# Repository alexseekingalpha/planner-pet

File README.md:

Planner Pet: By Alexander Smallwood
Welcome to my project - Planner pet! 
Inspired by my struggles with ADHD I wanted to mkae a deivce to motivate others and I to complete tasks regardless of what the task is. 
Take homework for example. Homework is so hard to complete as there is no instant reward, you must wait to finish the problem to recieve the dopamine of completing such homework. 
To fix this I hypothesise that a digital pet will create a bond to the user motivating them to complete tasks to keep the pet alive! Like a tamagotchi!

The process is simple and fun:
Complete tasks and your pet earns XP which lets it grow through life stages, and unlocks cosmetics. Miss tasks and it regresses eventually going dormant.
To enhance attachment, each pet is generated from a random seed so everyone has a unique pet!

Hardware:
MCU: Esp32-S3-Wroom-1-N8
Display: st7789 240x250 tft spi 
RTC: DS3231 
Power: 500mah lipo whith BQ24040 charging via USBC, TLV75801 ldo to regualate the power to the MCU
Input: 4 button dpad with + 2 standalone buttons for 'select' and 'back'
All KiCad files will be uploaded (Using KiCad 9)

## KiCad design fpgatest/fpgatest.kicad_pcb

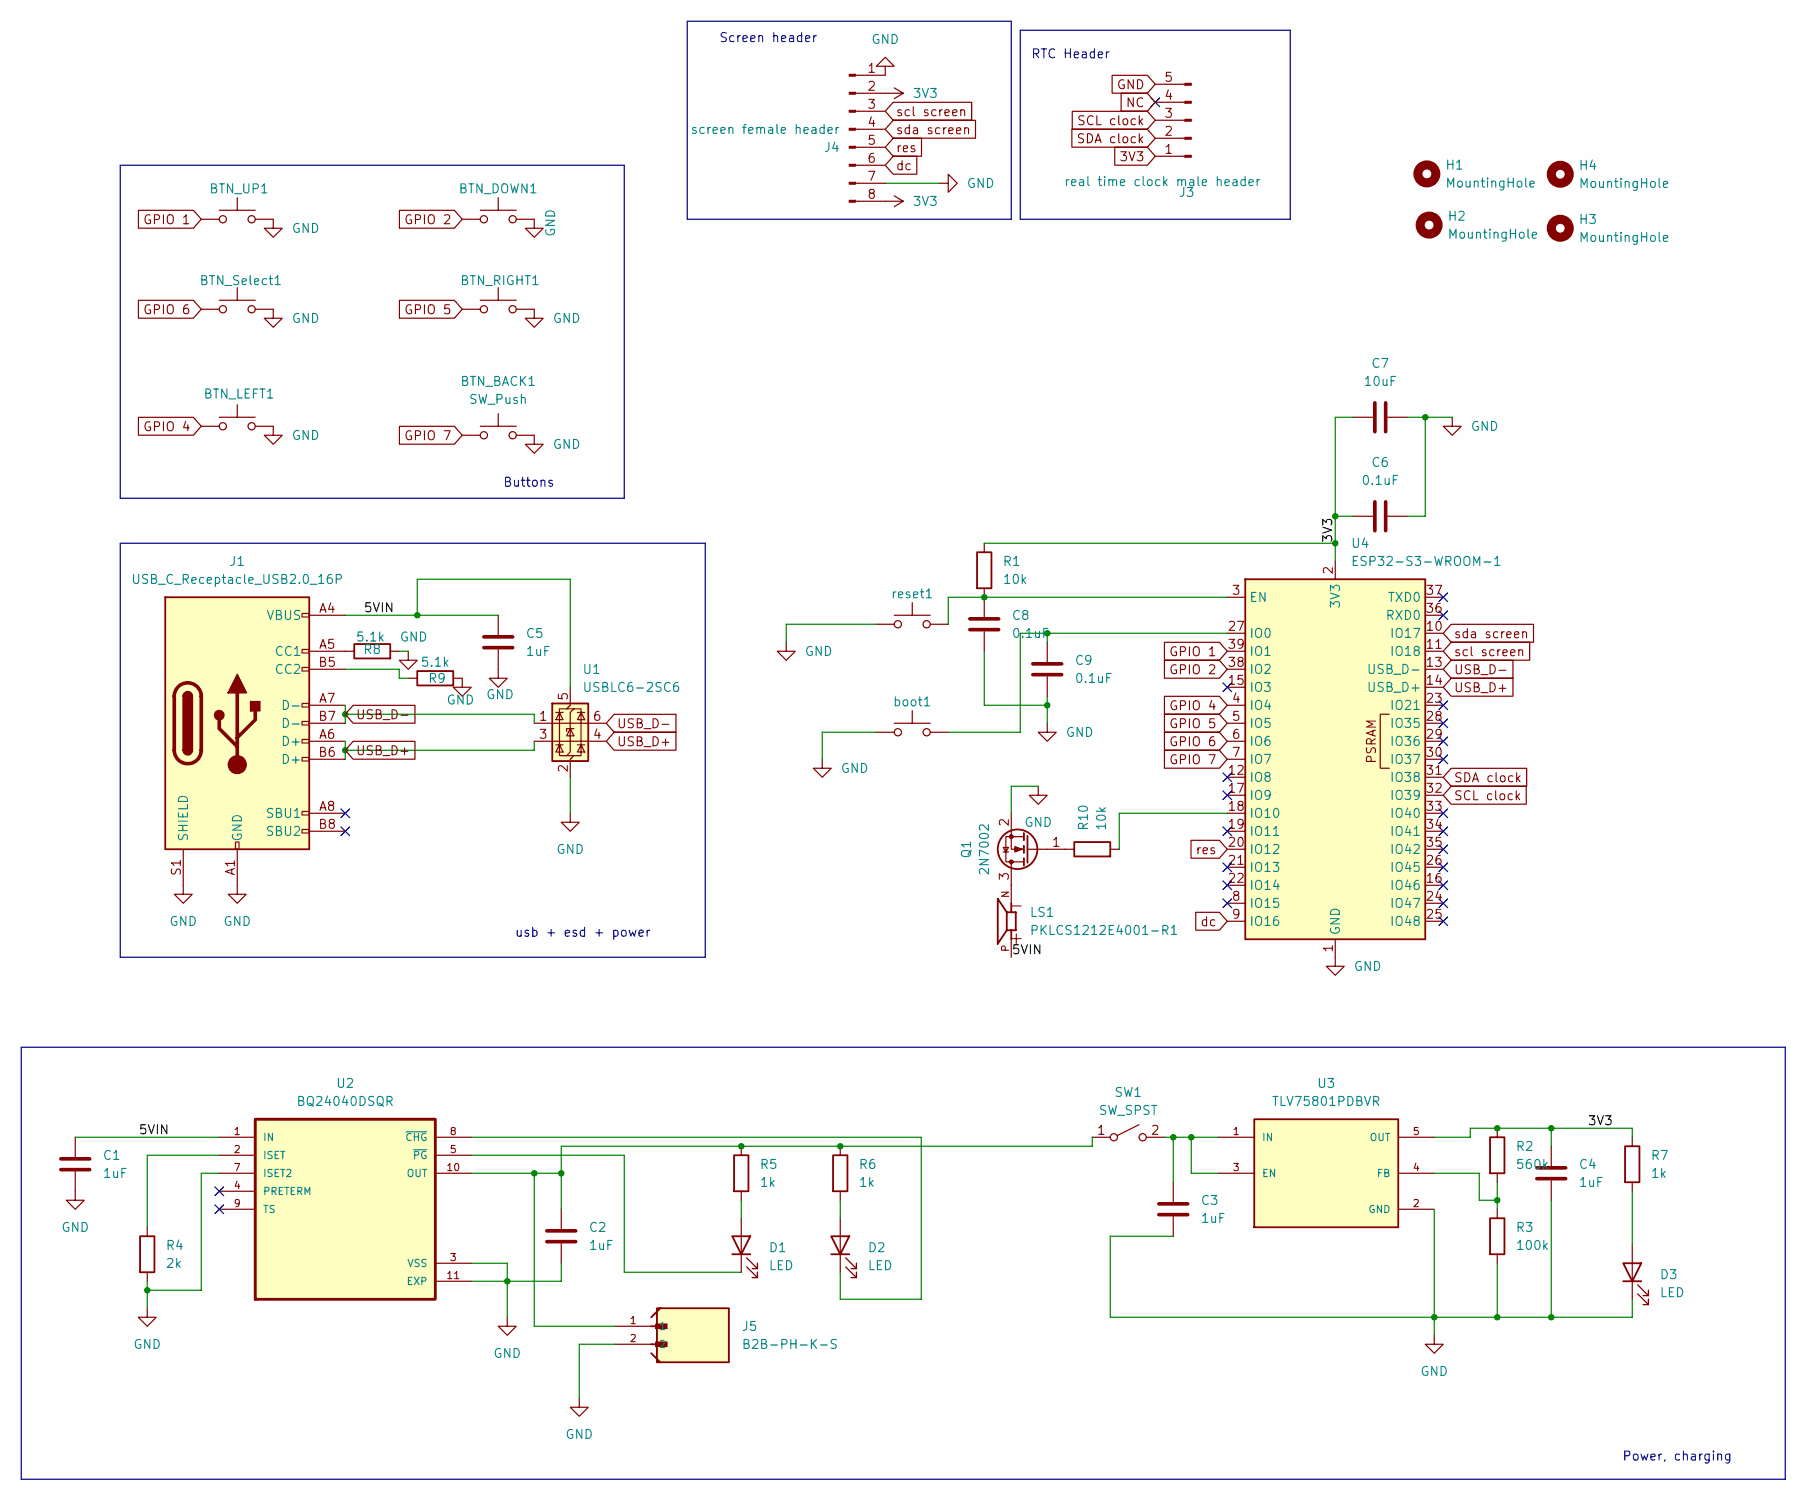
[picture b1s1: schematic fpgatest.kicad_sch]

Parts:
BTN_BACK1: SW_Push; SW_Push_1P1T_NO_CK_KMR2
BTN_DOWN1: SW_Push; SW_Push_1P1T_NO_CK_KMR2
BTN_LEFT1: SW_Push; SW_Push_1P1T_NO_CK_KMR2
BTN_RIGHT1: SW_Push; SW_Push_1P1T_NO_CK_KMR2
BTN_Select1: SW_Push; SW_Push_1P1T_NO_CK_KMR2
BTN_UP1: SW_Push; SW_Push_1P1T_NO_CK_KMR2
C1, C2, C3, C4, C5: 1uF; C_0603_1608Metric
C6, C8, C9: 0.1uF; C_0603_1608Metric
C7: 10uF; C_0603_1608Metric
D1, D2, D3: LED; LED_0603_1608Metric
H1, H2, H3, H4: MountingHole; MountingHole_2.2mm_M2
J1: USB_C_Receptacle_USB2.0_16P; USB_C_Receptacle_GCT_USB4105-xx-A_16P_TopMnt_Horizontal
J3: real time clock male header; PinHeader_1x05_P2.54mm_Vertical
J4: screen female header; PinSocket_1x08_P2.54mm_Vertical
J5: B2B-PH-K-S; JST_B2B-PH-K-S
LS1: PKLCS1212E4001-R1; SPKR_PKLCS1212E4001-R1; PARTREV January 22, 2018
Q1: 2N7002; SOT-23
R1, R10: 10k; R_0603_1608Metric
R2: 560k; R_0603_1608Metric
R3: 100k; R_0603_1608Metric
R4: 2k; R_0603_1608Metric
R5, R6, R7: 1k; R_0603_1608Metric
R8, R9: 5.1k; R_0603_1608Metric
SW1: SW_SPST; SW_SPDT_PCM12
U1: USBLC6-2SC6; SOT-23-6
U2: BQ24040DSQR; SON40P200X200X80-11N
U3: TLV75801PDBVR; SOT95P280X145-5N; PARTREV D
U4: ESP32-S3-WROOM-1
boot1: SW_Push; SW_Push_1P1T_NO_CK_KMR2
reset1: SW_Push; SW_Push_1P1T_NO_CK_KMR2

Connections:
3V3: C4.1, C6.1, C7.1, J3.1, J4.2, J4.8, R1.1, R2.1, R7.1, U3.5 (OUT), U4.2 (3V3)
/5VIN: C1.1, C5.1, J1.A4 (VBUS), J1.A9 (VBUS), J1.B4 (VBUS), J1.B9 (VBUS), LS1.P, U1.5 (VBUS), U2.1 (IN)
GND: BTN_BACK1.2, BTN_DOWN1.2, BTN_LEFT1.2, BTN_RIGHT1.2, BTN_Select1.2, BTN_UP1.2, C1.2, C2.2, C3.2, C4.2, C5.2, C6.2, C7.2, C8.2, C9.2, D3.1 (K), J1.A1 (GND), J1.A12 (GND), J1.B1 (GND), J1.B12 (GND), J1.S1 (SHIELD), J3.5, J4.1, J4.7, J5.2, Q1.2 (S), R3.2, R4.2, R8.2, R9.2, U1.2 (GND), U2.3 (VSS), U2.7 (ISET2), U2.11 (EXP), U3.2 (GND), U4.1 (GND), U4.40 (GND), U4.41 (GND), boot1.1, reset1.1
GPIO 1: BTN_UP1.1, U4.39 (IO1)
GPIO 2: BTN_DOWN1.1, U4.38 (IO2)
GPIO 4: BTN_LEFT1.1, U4.4 (IO4)
GPIO 5: BTN_RIGHT1.1, U4.5 (IO5)
GPIO 6: BTN_Select1.1, U4.6 (IO6)
GPIO 7: BTN_BACK1.1, U4.7 (IO7)
NC: J3.4
unnamed: D1.2 (A), R5.2
unnamed: D1.1 (K), U2.5 (~PG)
unnamed: D2.2 (A), R6.2
unnamed: D2.1 (K), U2.8 (~CHG)
unnamed: D3.2 (A), R7.2
unnamed: J1.A5 (CC1), R8.1
unnamed: J1.B5 (CC2), R9.1
unnamed: LS1.N, Q1.3 (D)
unnamed: Q1.1 (G), R10.1
unnamed: C2.1, J5.1, R5.1, R6.1, SW1.1 (A), U2.10 (OUT)
unnamed: C3.1, SW1.2 (B), U3.1 (IN), U3.3 (EN)
unnamed: R4.1, U2.2 (ISET)
unnamed: R2.2, R3.1, U3.4 (FB)
unnamed: C8.1, R1.2, U4.3 (EN), reset1.2
unnamed: C9.1, U4.27 (IO0), boot1.2
unnamed: R10.2, U4.18 (IO10)
SCL clock: J3.3, U4.32 (IO39)
SDA clock: J3.2, U4.31 (IO38)
USB_D+: J1.A6 (D+), J1.B6 (D+), U1.3 (I/O2), U1.4 (I/O2), U4.14 (USB_D+)
USB_D-: J1.A7 (D-), J1.B7 (D-), U1.1 (I/O1), U1.6 (I/O1), U4.13 (USB_D-)
dc: J4.6, U4.9 (IO16)
res: J4.5, U4.20 (IO12)
scl screen: J4.3, U4.11 (IO18)
sda screen: J4.4, U4.10 (IO17)

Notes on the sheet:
Screen header
Buttons
RTC Header
Power, charging
usb + esd + power

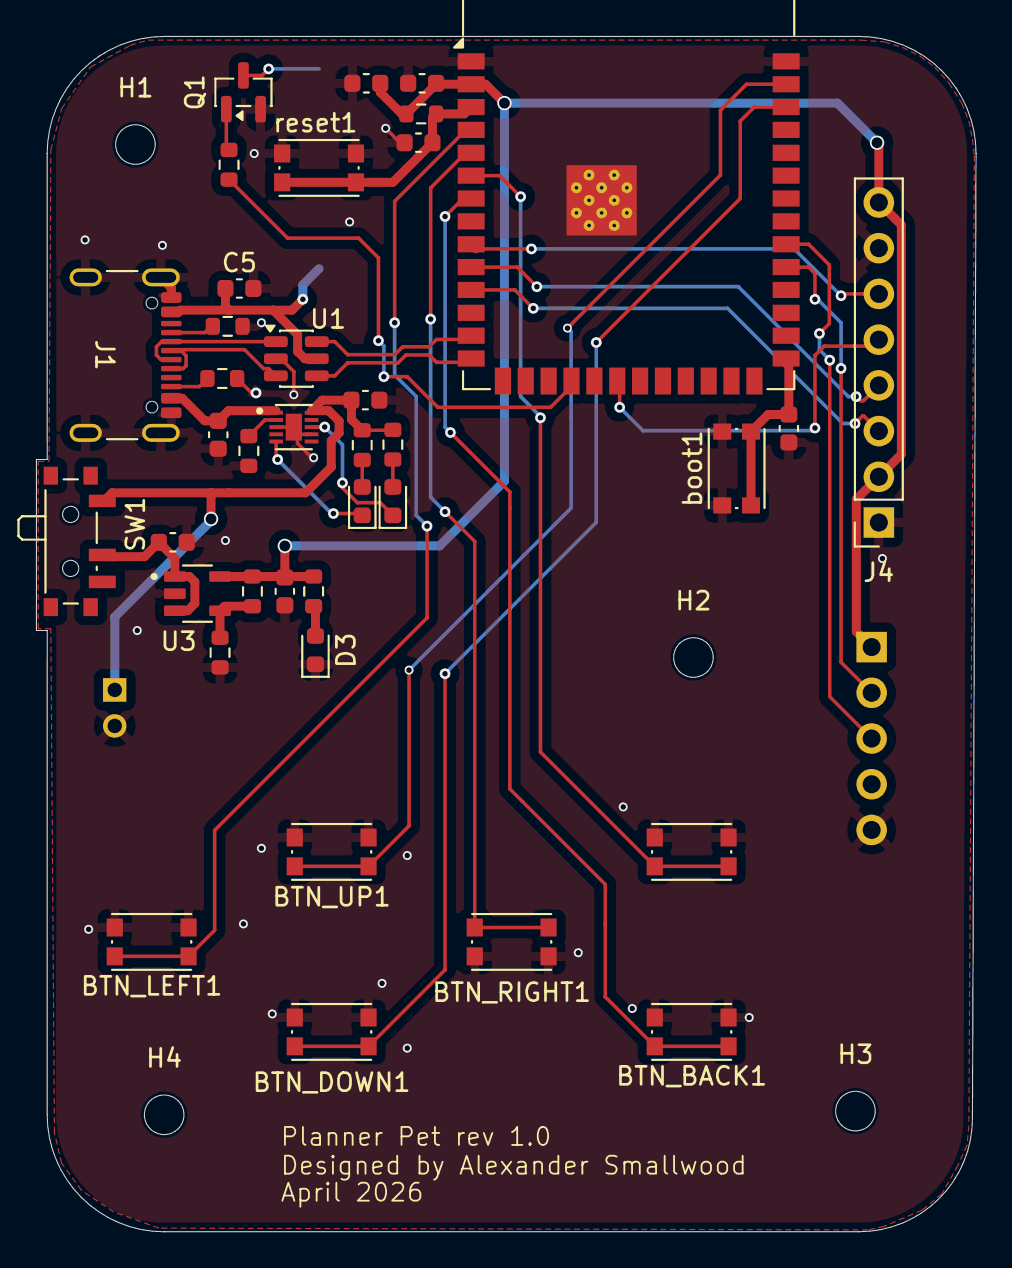
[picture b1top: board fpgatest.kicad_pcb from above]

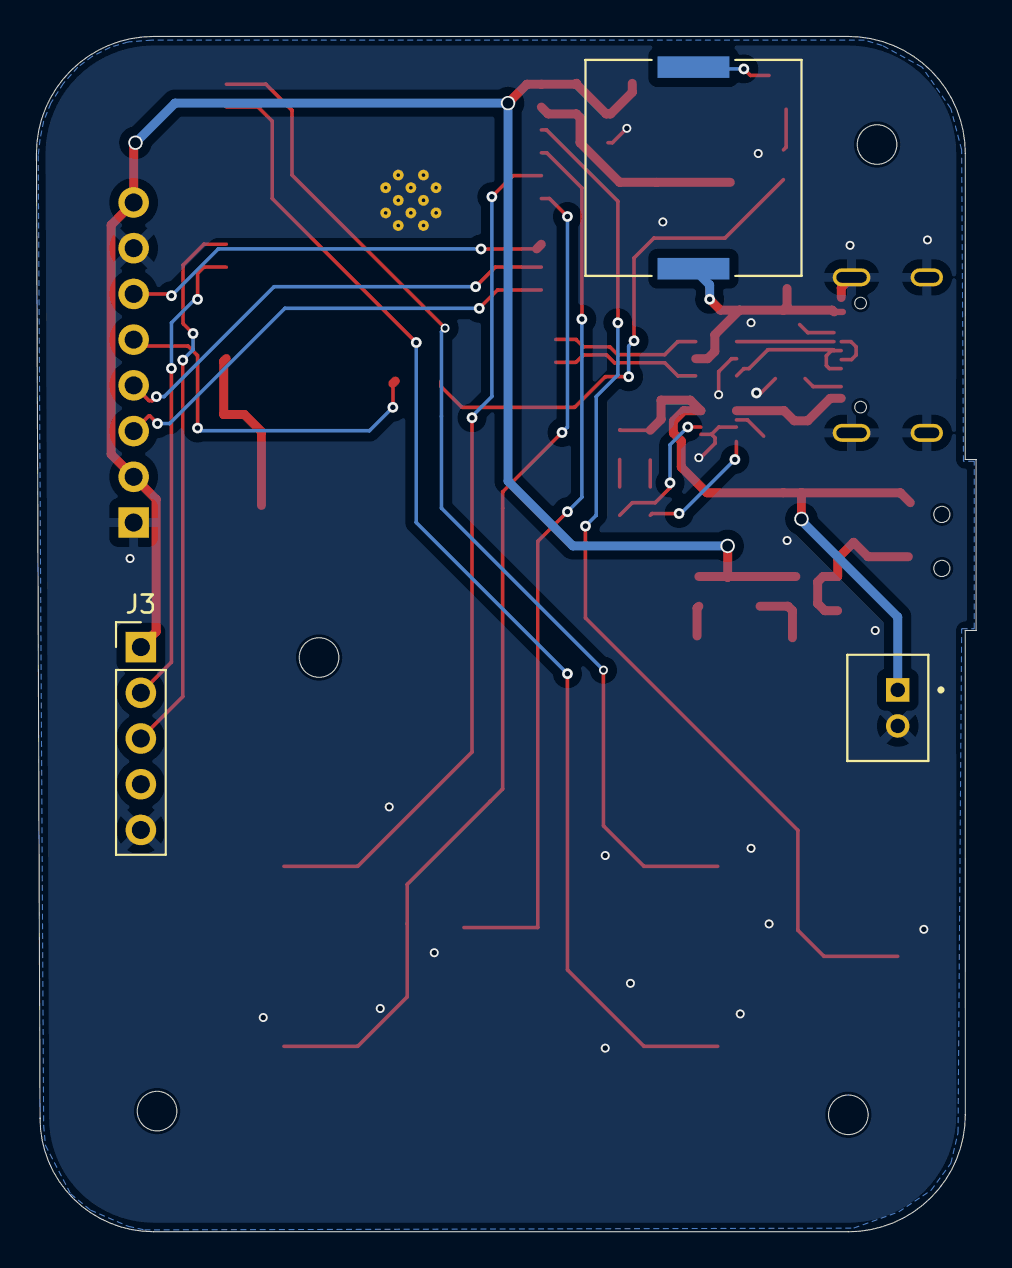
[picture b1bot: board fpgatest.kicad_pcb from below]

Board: 2 copper layers, 52.2 x 66.4 mm, 45 parts (3 on the bottom side), 33 nets.

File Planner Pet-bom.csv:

Name,Purpose,Quantity,Total Cost (USD),Link,Distributor
"1k Resistor 0603","LED current limiting (R5,R6,R7)",3,0.03,"https://www.lcsc.com/product-detail/C21190.html","LCSC"
"10k Resistor 0603","Pulldown / pullup (R1,R10)",2,0.03,"https://www.lcsc.com/product-detail/C25804.html","LCSC"
"5.1k Resistor 0603","USB CC pulldown (R8,R9)",2,0.03,"https://www.lcsc.com/product-detail/C23186.html","LCSC"
"2k Resistor 0603","BQ24040 charge current set (R4)",1,0.03,"https://www.lcsc.com/product-detail/C22975.html","LCSC"
"100k Resistor 0603","LDO feedback divider (R3)",1,0.03,"https://www.lcsc.com/product-detail/C25803.html","LCSC"
"560k Resistor 0603","LDO feedback divider (R2)",1,0.03,"https://www.lcsc.com/product-detail/C23203.html","LCSC"
"1uF Capacitor 0603","Decoupling / bypass (C1-C5)",5,0.15,"https://www.lcsc.com/product-detail/C15849.html","LCSC"
"100nF Capacitor 0603","Decoupling (C6,C8,C9)",3,0.06,"https://www.lcsc.com/product-detail/C14663.html","LCSC"
"10uF Capacitor 0603","LDO output capacitor (C7)",1,0.16,"https://www.lcsc.com/product-detail/C19702.html","LCSC"
"Red LED 0603 (150060RS75000)","Charge status indicator (D1)",1,1.34,"https://www.lcsc.com/product-detail/C3030991.html","LCSC"
"Green LED 0603 (150060GS75000)","Power good indicator (D2)",1,1.40,"https://www.lcsc.com/product-detail/C5252984.html","LCSC"
"Blue LED 0603 (150060BS75000)","General indicator (D3)",1,1.12,"https://www.lcsc.com/product-detail/C5197644.html","LCSC"
"ESP32-S3-WROOM-1-N16R8","Main MCU - WiFi/BLE SoC (U4)",1,10.38,"https://www.lcsc.com/product-detail/C2913202.html","LCSC"
"BQ24040DSQR","Li-ion battery charger IC (U2)",1,2.05,"https://www.lcsc.com/product-detail/C81080.html","LCSC"
"USBLC6-2SC6","USB ESD protection (U1)",1,0.77,"https://www.lcsc.com/product-detail/C7519.html","LCSC"
"TLV75801PDBVR","3.3V LDO regulator (U3)",1,0.56,"https://www.lcsc.com/product-detail/C2877852.html","LCSC"
"2N7002","Buzzer MOSFET driver (Q1)",1,0.13,"https://www.lcsc.com/product-detail/C8545.html","LCSC"
"PKLCS1212E4001-R1","Passive piezo buzzer (LS1)",1,1.54,"https://www.lcsc.com/product-detail/C113159.html","LCSC"
"KMR211GLFS","Tactile switches - navigation + boot/reset",8,8.32,"https://www.lcsc.com/product-detail/C221675.html","LCSC"
"PCM12SMTR","Power slide switch (SW1)",1,2.36,"https://www.lcsc.com/product-detail/C221841.html","LCSC"
"USB4105-GF-A","USB-C receptacle 16pin (J1)",1,0.20,"https://www.lcsc.com/product-detail/C2765186.html","LCSC"
"B2B-PH-K-S(LF)(SN)","JST PH 2-pin battery connector (J5)",1,0.10,"https://www.lcsc.com/product-detail/C131337.html","LCSC"
"KH-2.54FH-1X8P-H8.5","1x8 female header for screen (J4)",1,0.21,"https://www.lcsc.com/product-detail/C2905417.html","LCSC"
"KH-2.54PH180-1X5P-L11.5","1x5 male header for RTC (J3)",1,0.08,"https://www.lcsc.com/product-detail/C2932699.html","LCSC"

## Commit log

2026-04-09 Code for the planner pet!
    A good prototype code for the planner pet!
2026-04-09 Add files via upload
    Keep in mind the files are called "fpgatest" as this project started as that but I switched to this project but used the same kicad file on accident, can change in the future if its an issue
